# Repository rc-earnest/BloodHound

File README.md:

Please read all of the READ files within the various folders as they may contain information as to what files you need to grab in the future.

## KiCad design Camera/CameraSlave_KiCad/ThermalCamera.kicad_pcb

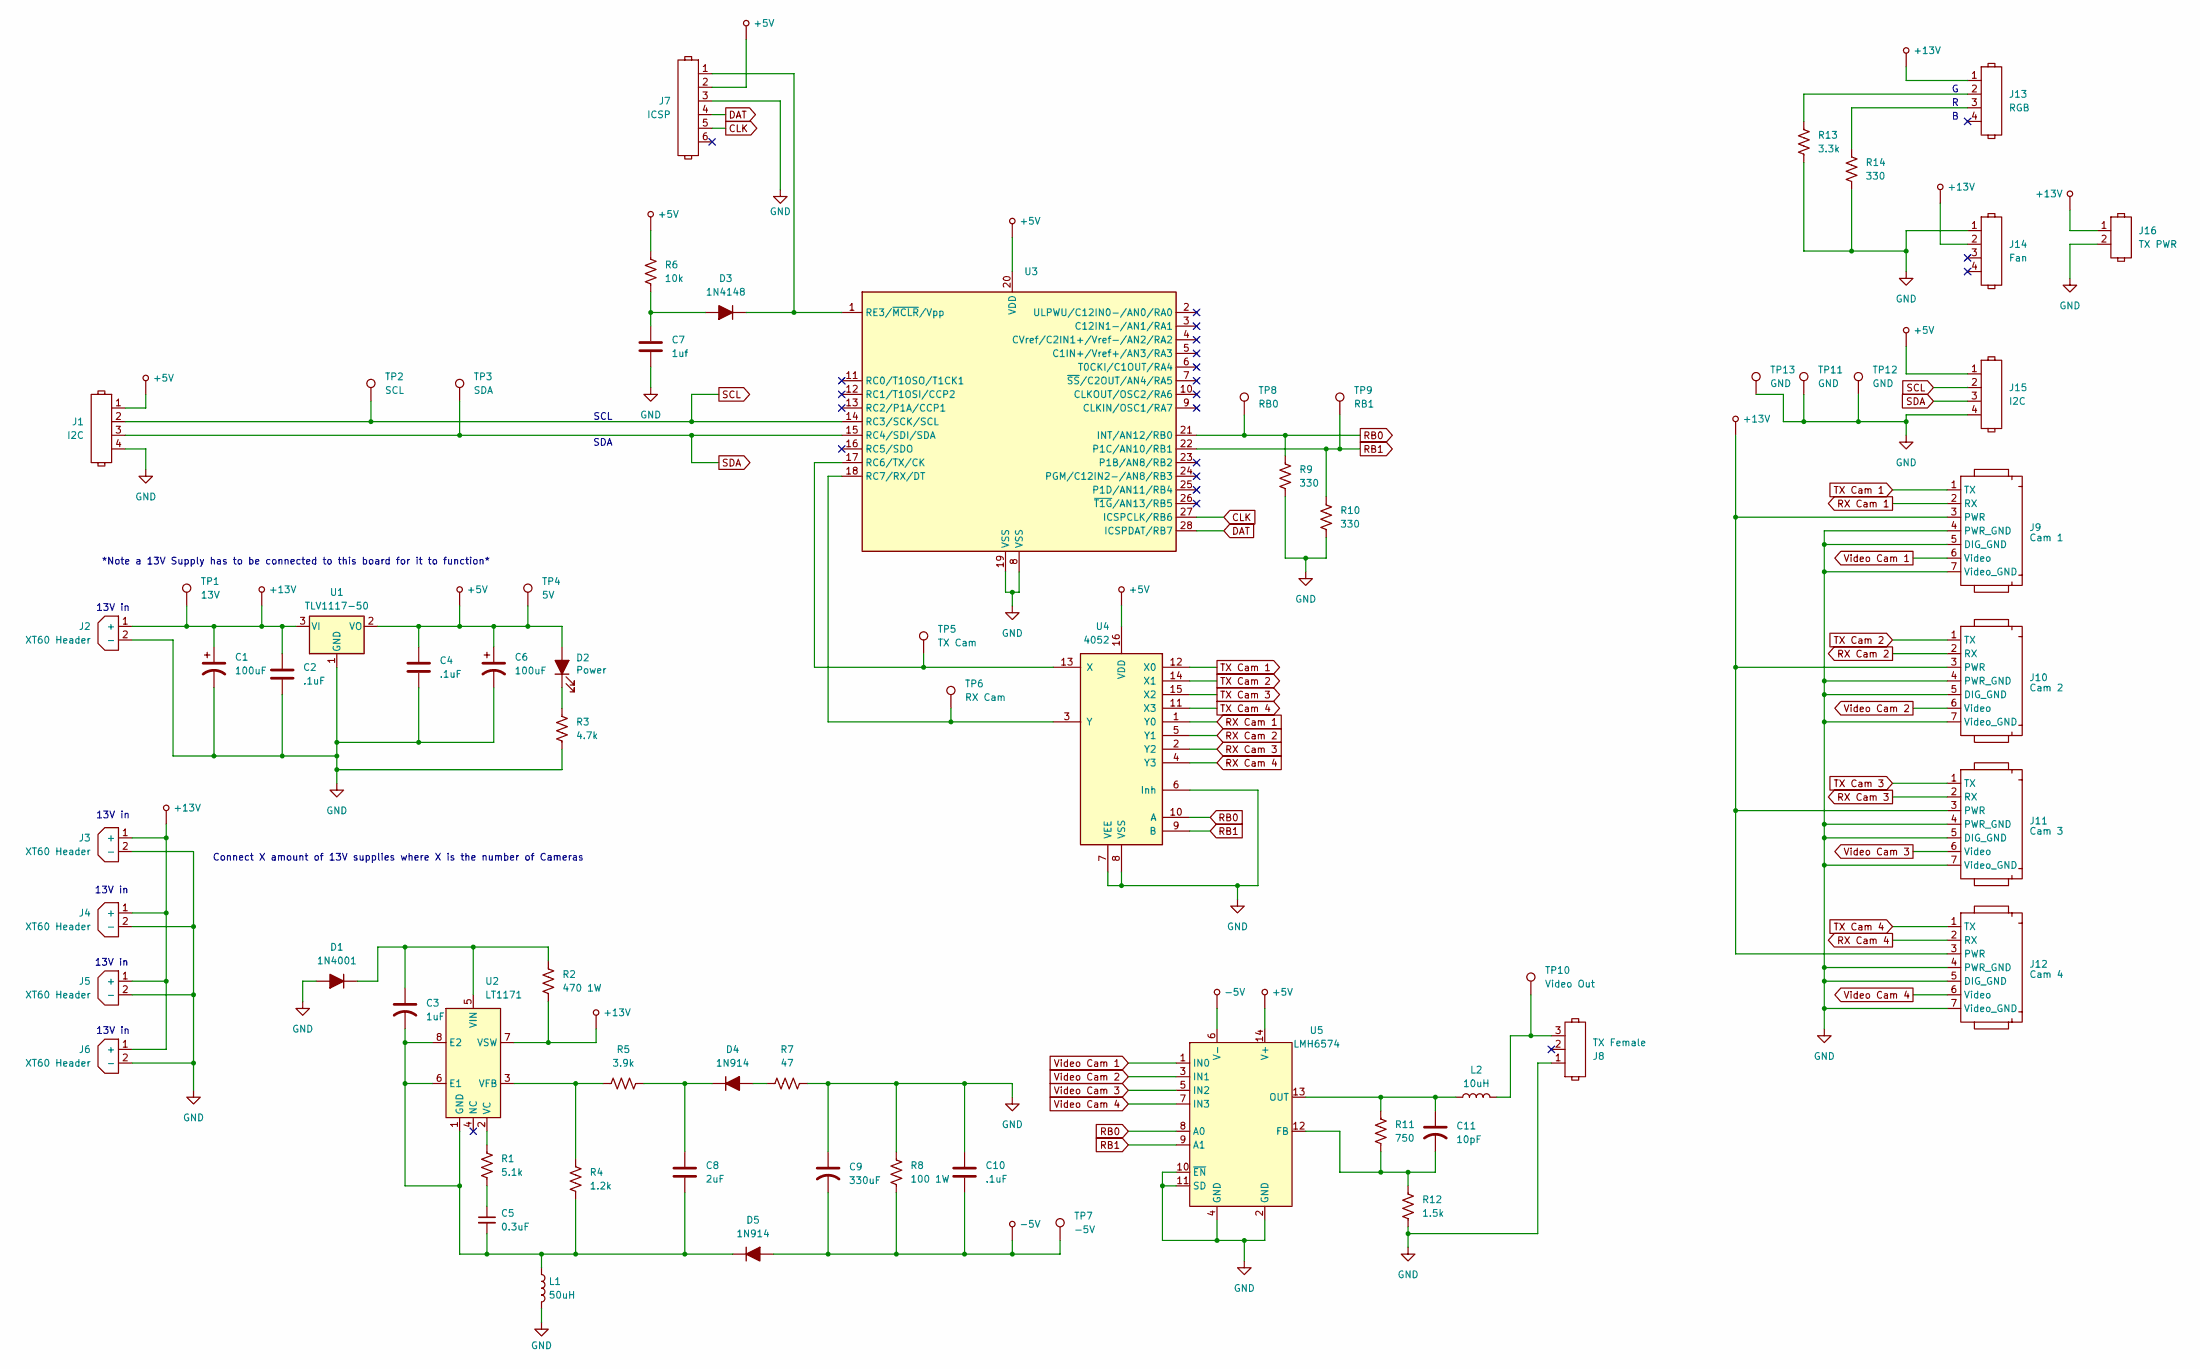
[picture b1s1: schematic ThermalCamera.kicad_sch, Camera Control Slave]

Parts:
C1, C6: 100uF; C_Radial_D5.0mm_H11.0mm_P2.00mm
C2, C4, C10: .1uF; 0805
C3: 1uF; 0805
C5: 0.3uF; 0805
C7: 1uf; 0805
C8: 2uF; 0805
C9: 330uF; C_Radial_D8.0mm_H11.5mm_P3.50mm
C11: 10pF; 0805
D1: 1N4001; DIODE_0805
D2: Power; DIODE_0805
D3: 1N4148; DIODE_0805
D4, D5: 1N914; DIODE_0805
J1, J15: I2C; Header_1_x_4
J2, J3, J4, J5, J6: XT60 Header; XT-60 Power Male (Load Side)
J7: ICSP; Header_1_x_6
J8: TX Female; Header_1_x_3
J9: Cam 1; Header_1_x_7
J10: Cam 2; Header_1_x_7
J11: Cam 3; Header_1_x_7
J12: Cam 4; Header_1_x_7
J13: RGB; Header_1_x_4
J14: Fan; Header_1_x_4
J16: TX PWR; Header_1_x_2
L1: 50uH; 78404064680
L2: 10uH; 0805
R1: 5.1k; 0805
R2: 470 1W; R_Axial_DIN0309_L9.0mm_D3.2mm_P12.70mm_Horizontal
R3: 4.7k; 0805
R4: 1.2k; 0805
R5: 3.9k; 0805
R6: 10k; 0805
R7: 47; 0805
R8: 100 1W; R_Axial_DIN0309_L9.0mm_D3.2mm_P12.70mm_Horizontal
R9, R10, R14: 330; 0805
R11: 750; 0805
R12: 1.5k; 0805
R13: 3.3k; 0805
TP1: 13V; Header_1_x_1
TP2: SCL; Header_1_x_1
TP3: SDA; Header_1_x_1
TP4: 5V; Header_1_x_1
TP5: TX Cam; Header_1_x_1
TP6: RX Cam; Header_1_x_1
TP7: -5V; Header_1_x_1
TP8: RB0; Header_1_x_1
TP9: RB1; Header_1_x_1
TP10: Video Out; Header_1_x_1
TP11, TP12, TP13: GND; Header_1_x_1
U1: TLV1117-50
U2: LT1171; LT1172
U3: PIC16F883
U4: 4052; CD4052BPWR
U5: LMH6574

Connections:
+5V: C4.1, C6.1, D2.2 (A), J1.1, J7.2, J15.1, R6.1, TP4.1, U1.2 (VO), U3.20 (VDD), U4.16 (VDD), U5.14 (V+)
+13V: C1.1, C2.1, J2.1 (+), J3.1 (+), J4.1 (+), J5.1 (+), J6.1 (+), J9.3 (PWR), J10.3 (PWR), J11.3 (PWR), J12.3 (PWR), J13.1, J14.2, J16.1, R2.2, TP1.1, U1.3 (VI), U2.7 (VSW)
-5V: C9.2, C10.2, D5.2 (A), R8.2, TP7.1, U5.6 (V-)
CLK: J7.5, U3.27 (ICSPCLK/RB6)
DAT: J7.4, U3.28 (ICSPDAT/RB7)
GND: C1.2, C2.2, C4.2, C6.2, C7.2, C9.1, C10.1, D1.2 (A), J1.4, J2.2 (-), J3.2 (-), J4.2 (-), J5.2 (-), J6.2 (-), J7.3, J8.1, J9.4 (PWR_GND), J9.5 (DIG_GND), J9.7 (Video_GND), J10.4 (PWR_GND), J10.5 (DIG_GND), J10.7 (Video_GND), J11.4 (PWR_GND), J11.5 (DIG_GND), J11.7 (Video_GND), J12.4 (PWR_GND), J12.5 (DIG_GND), J12.7 (Video_GND), J14.1, J15.4, J16.2, L1.2, R3.2, R7.2, R8.1, R9.2, R10.2, R12.2, R13.2, R14.2, TP11.1, TP12.1, TP13.1, U1.1 (GND), U3.8 (VSS), U3.19 (VSS), U4.6 (Inh), U4.7 (VEE), U4.8 (VSS), U5.2 (GND), U5.4 (GND), U5.10 (~EN), U5.11 (SD)
unnamed: C5.1, R1.2
unnamed: C3.1, D1.1 (K), R2.1, U2.5 (VIN)
unnamed: D2.1 (K), R3.1
unnamed: C7.1, D3.2 (A), R6.2
unnamed: D3.1 (K), J7.1, U3.1 (RE3/~MCLR/Vpp)
unnamed: D4.2 (A), R7.1
unnamed: C8.1, D4.1 (K), R5.2
unnamed: C3.2, C5.2, C8.2, D5.1 (K), L1.1, R4.2, U2.1 (GND), U2.6 (E1), U2.8 (E2)
unnamed: J8.3, L2.2, TP10.1
unnamed: J13.2, R13.1
unnamed: J13.3, R14.1
unnamed: R1.1, U2.2 (VC)
unnamed: R4.1, R5.1, U2.3 (VFB)
unnamed: TP5.1, U3.17 (RC6/TX/CK), U4.13 (X)
unnamed: TP6.1, U3.18 (RC7/RX/DT), U4.3 (Y)
unnamed: C11.2, R11.2, R12.1, U5.12 (FB)
unnamed: C11.1, L2.1, R11.1, U5.13 (OUT)
RB0: R9.1, TP8.1, U3.21 (INT/AN12/RB0), U4.10 (A), U5.8 (A0)
RB1: R10.1, TP9.1, U3.22 (P1C/AN10/RB1), U4.9 (B), U5.9 (A1)
RX Cam 1: J9.2 (RX), U4.1 (Y0)
RX Cam 2: J10.2 (RX), U4.5 (Y1)
RX Cam 3: J11.2 (RX), U4.2 (Y2)
RX Cam 4: J12.2 (RX), U4.4 (Y3)
SCL: J1.2, J15.2, TP2.1, U3.14 (RC3/SCK/SCL)
SDA: J1.3, J15.3, TP3.1, U3.15 (RC4/SDI/SDA)
TX Cam 1: J9.1 (TX), U4.12 (X0)
TX Cam 2: J10.1 (TX), U4.14 (X1)
TX Cam 3: J11.1 (TX), U4.15 (X2)
TX Cam 4: J12.1 (TX), U4.11 (X3)
Video Cam 1: J9.6 (Video), U5.1 (IN0)
Video Cam 2: J10.6 (Video), U5.3 (IN1)
Video Cam 3: J11.6 (Video), U5.5 (IN2)
Video Cam 4: J12.6 (Video), U5.7 (IN3)

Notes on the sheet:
13V in
Connect X amount of 13V supplies where X is the number of Cameras
SDA
SCL
*Note a 13V Supply has to be connected to this board for it to function*

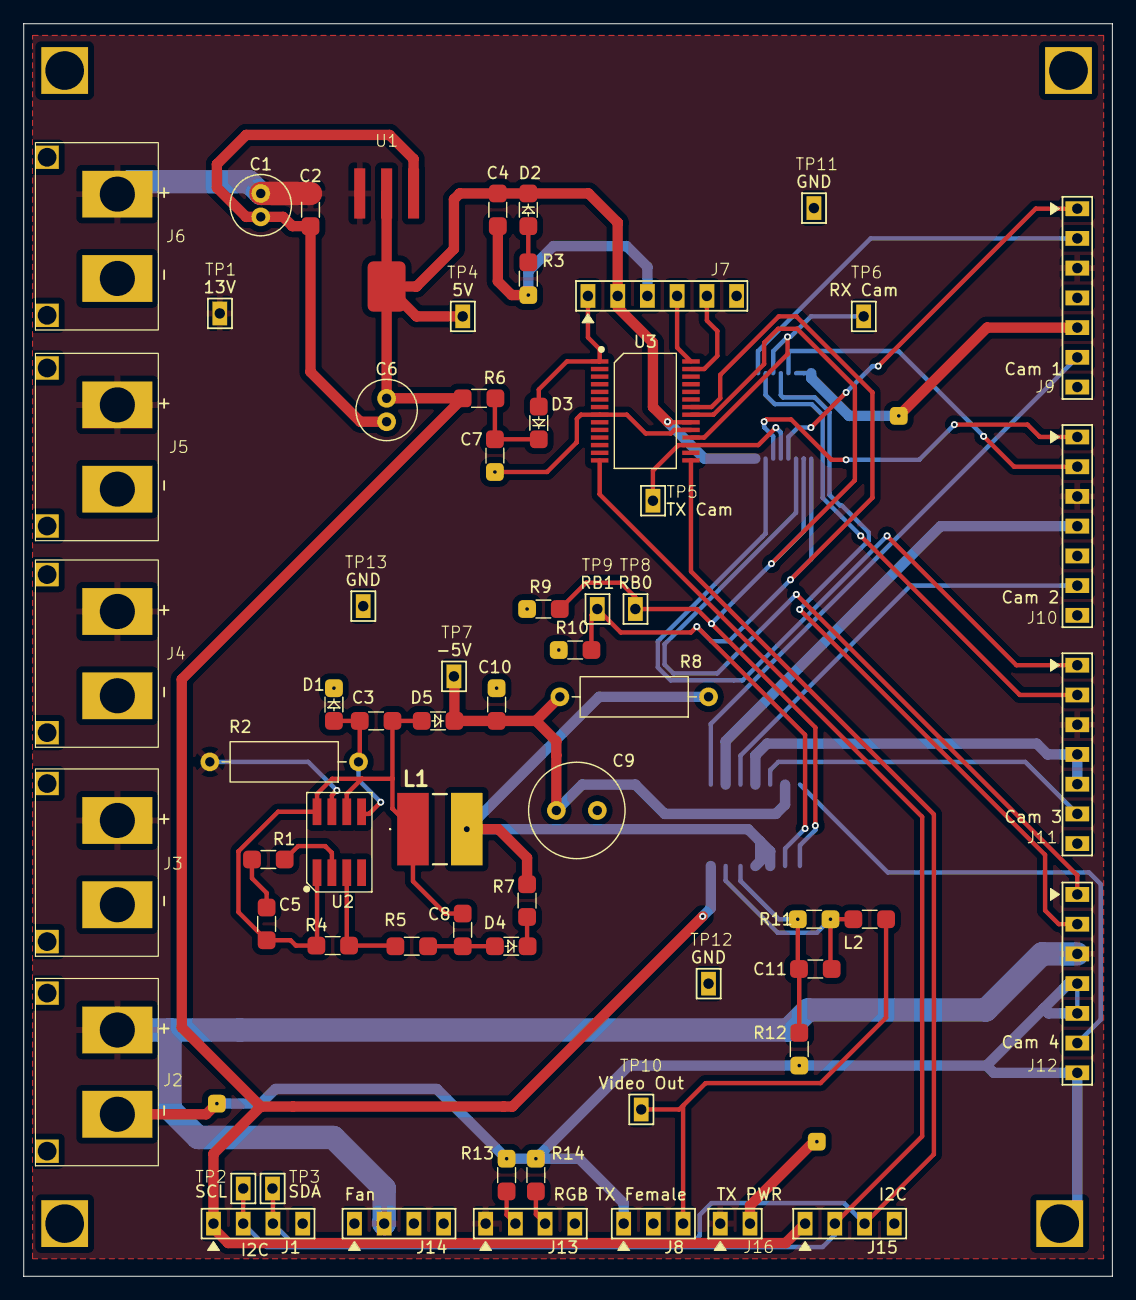
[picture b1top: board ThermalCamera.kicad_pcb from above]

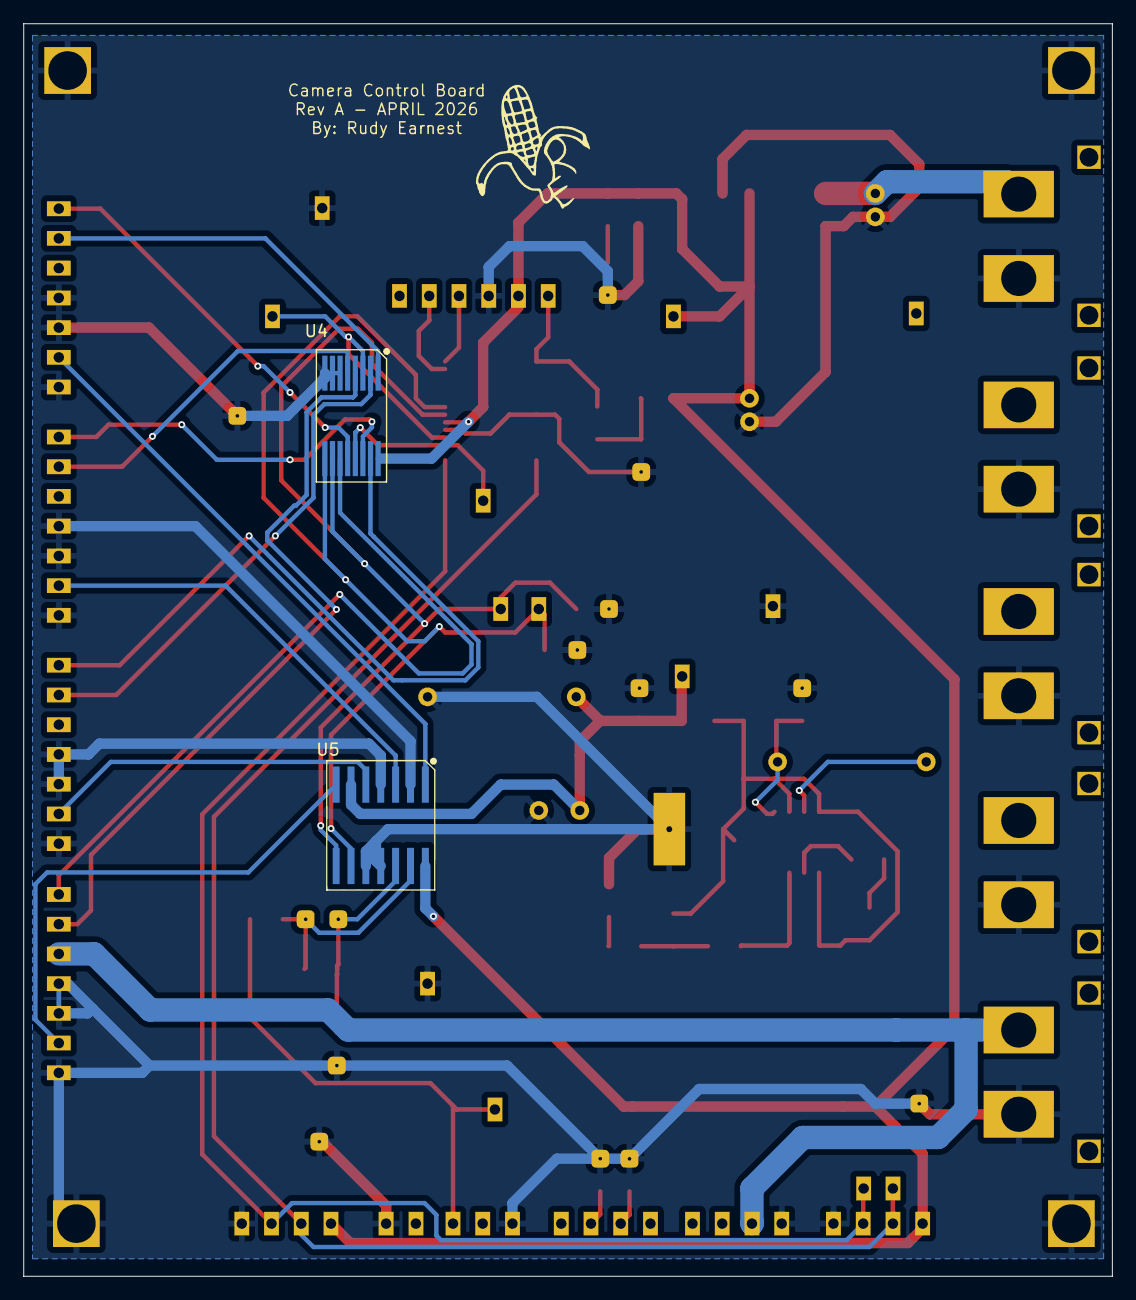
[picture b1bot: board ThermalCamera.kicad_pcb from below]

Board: 2 copper layers, 93.0 x 107.0 mm, 66 parts (2 on the bottom side), 39 nets.

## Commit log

2026-04-06 adding read me
2026-04-06 adding master code files to main
2026-04-06 adding project org folders
2026-04-06 adding remote testing software
2026-04-06 migrating existing camera files from old git repo
2026-04-08 working code for Slave Camera board reset doesn't work but has same byte string from last semester will investigate at a later date
2026-04-14 Adding more to the KiCad schematic
2026-04-16 adding finished board schematic as well as PCB design
2026-04-20 adding kicad gerbers, PCB and final schematic for REV A
2026-04-20 Adding the master code to implement a two address slave recieve system, the addresses can be changed at a later date
2026-04-20 added comments to C Camera slave code to say what is happening
2026-04-22 Add resource folder for PDFs and other applicable files for research/testing
2026-04-27 Add PIC16F1788 datasheet to resources folder
2026-04-27 Adding functionality to the zoom for the sony cameras to stop the zoom if it has started, also fixed the homing of the camera
2026-04-28 Init C# WinForm for reading/parsing data from LiDAR
2026-04-28 Still working on functionality
2026-04-28 Add .gitignore file
2026-04-28 Added user control for how often data is acquired, along with duration display
2026-04-28 Working on adding read data/write to file functions
2026-04-28 Added preliminary code to save read data, added function to recheck/refresh serial ports, Identified bug with reading serial data
2026-04-28 Added documentation/comments for code
2026-04-28 Added simplified logic to enable/disable timer and controls; Added "safe" way to cleanly exit form and close Serial port(s) used
2026-04-28 Added better logic to control the file path, fixed bug that prevented writing/saving to file; Added cleaner logic to retrieve and write data to file
2026-04-28 Added more information to the written file for easier debugging
2026-04-28 Revert "Added more information to the written file for easier debugging"
    This reverts commit 58cb08dee61864d992f39cf30426e9644ed98b69.
2026-04-28 Unable to store/read data currently, something wrong with one of those methods
2026-04-28 Restructuring; Starting to think that the timer idea wasn't the best...
2026-04-28 Working on stepping away from the timer idea and moving towards event-based handling for when data is received
2026-04-29 Troubleshooting lack of data reception
2026-04-29 Program now shows data being received when tested with different device
2026-04-29 Reverted back to original settings and added better indicators for debugging
2026-04-29 Display somewhat works now; Attempting to "parse"/split through data for easier viewing/management
2026-04-29 Working state; File writes correctly and disregards "split" packets; Removed unused code/variables
2026-04-29 Copied sample log to main directory for ease of access
2026-04-29 Scrapping the idea of having two formats and working to display a singular one
2026-04-29 Removed unused code
2026-04-29 Working on logic to convert and display relevant received LiDAR data
2026-04-29 Preliminary data decoding is up, but has several bugs
2026-04-30 Changed direction for the analog stick so flow aligns with what is seen on the receiver
2026-04-30 reorganized the KiCad schematic for the camera a little bit
2026-04-30 Restructured so that converted display would update quicker; Added better visuals for diagnostic strip; Made note of bugged data conversion method
2026-04-30 Implemented multiple try-catches to prevent crashing and provide error messages for user
2026-04-30 Revert "Implemented multiple try-catches to prevent crashing and provide error messages for user"
    This reverts commit 6c691c1938ea94fa45bdc98662a71e170157dbba.
2026-04-30 Added better logic to prevent crashing and improved (slightly) visual data format. Displayed translated data is still incorrect/needs to be reassessed/tuned, but is "functional"
2026-04-30 Updated the GUI for better readability for (bugged) data
2026-04-30 GUI changes again. Prevents user from resizing form
2026-04-30 Added project header
2026-04-30 Added reference log file for serial LiDAR data
    Intended to aid in showing what data was recorded with the C# program via USB/UART.
2026-04-30 Moved header to the top
2026-04-30 Add designed LiDAR schematics and untracked files
2026-04-30 Adding better documentation and working on fixing bugs for data conversion
2026-04-30 Added much more efficient way to display data; still bugged, but making progress
2026-04-30 changing the master code to give the drive slave the correct information. This will need to be changed at a later date to also give the joystick buttons as this will be used for the headlights
2026-05-01 Uploaded designs and important data
2026-05-01 added new files
2026-05-01 made read file more clear
2026-05-01 adding slave drive code to the drive folder
2026-05-03 adding text to READ in camera folder
2026-05-04 Uploaded Pics
    Uploaded Measurements and Console Setup that was used for both base and rover piksi
2026-05-04 Create Measurements and Setup
2026-05-04 added measurement and setup files
2026-05-04 syncing with main
2026-05-06 Fixed bug for infinite message boxes
2026-05-06 Added final note/message for future user
2026-05-06 adding all leftover changes
2026-05-06 trying to figure out the test form with git
2026-05-07 Final commit/push
2026-05-07 Adding Aux sensors presentation, report and letter of transmittal
2026-05-07 added project report and presentation
2026-05-07 Add files via upload
    Added Bloodhound Capstone report, Bloodhound BOM (excluding camera stuff), Master main schematic, Slave dev schematic, and Uni remote schematic
2026-05-07 Add files via upload
    added report, bom, presentation, and all 3 board schematics
2026-05-07 updated slave code to reflect final code
